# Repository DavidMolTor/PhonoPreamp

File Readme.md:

# Phono Preamplifier

A simple and precise phono preamplifier with a linear power supply.

## Introduction

This project contains the design for a phono preamplifier to be used with moving magnet capsules. It is optimized for low noise and distortion levels and has an accurate RIAA equalization stage.

The project also contains the design of a dual rail linear power supply in order to achive the lowest possible supply noise while keeping costs low.

## Features

 - Compact form factor.

 - Precise RIAA equalization.

 - Low-noise linear power supply.

 - High-performance audio components.

 - Modular design for other applications.

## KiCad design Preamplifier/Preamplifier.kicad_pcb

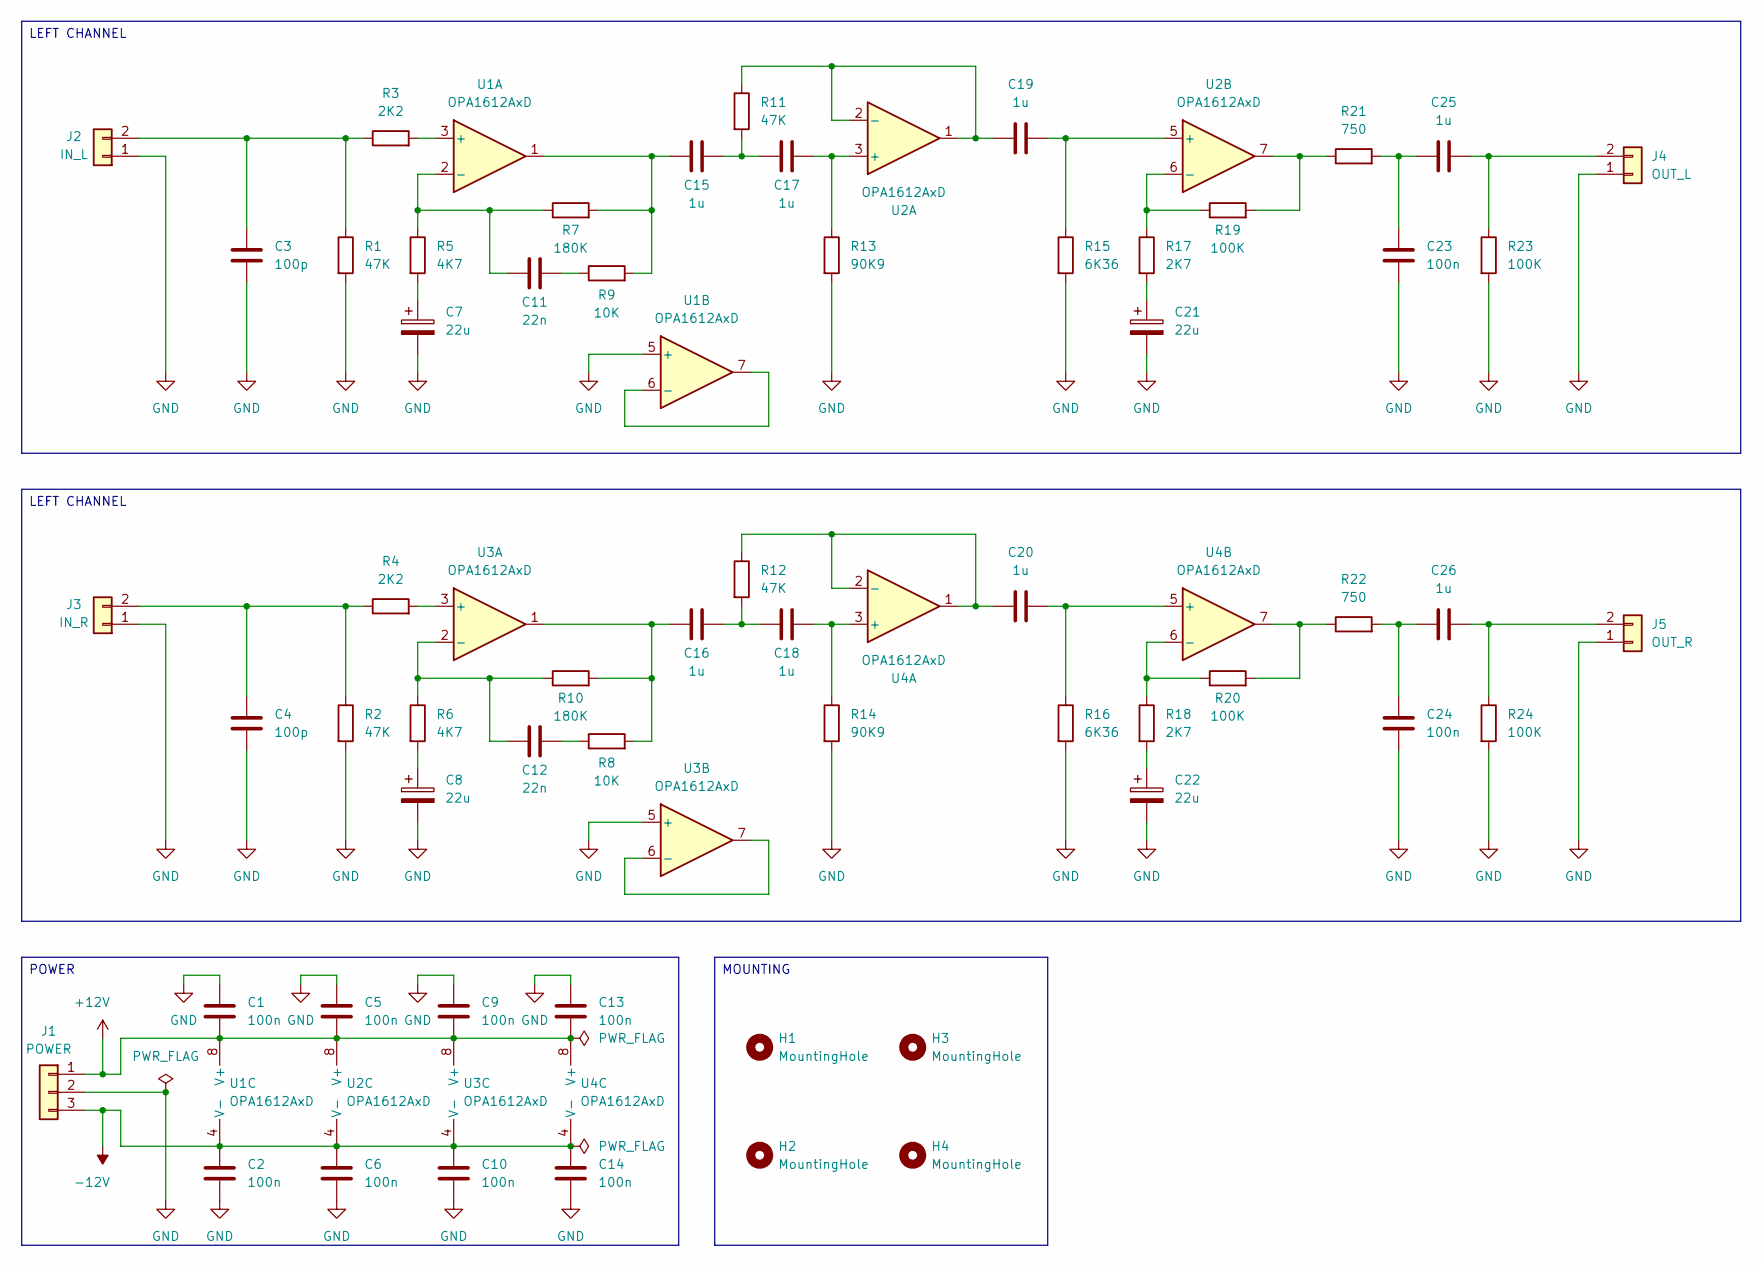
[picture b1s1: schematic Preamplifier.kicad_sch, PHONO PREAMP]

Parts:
C1, C2, C5, C6, C9, C10, C13, C14, C23, C24: 100n; C_0805_2012Metric_Pad1.18x1.45mm_HandSolder
C3, C4: 100p; C_0805_2012Metric_Pad1.18x1.45mm_HandSolder
C7, C8, C21, C22: 22u; CP_Elec_6.3x5.8
C11, C12: 22n; C_0805_2012Metric_Pad1.18x1.45mm_HandSolder
C15, C16, C17, C18, C19, C20, C25, C26: 1u; C_0805_2012Metric_Pad1.18x1.45mm_HandSolder
H1, H2, H3, H4: MountingHole; MountingHole_3.2mm_M3
J1: POWER; Molex_KK-254_1x03_P2.54mm_Vertical
J2: IN_L; Molex_KK-254_1x02_P2.54mm_Vertical
J3: IN_R; Molex_KK-254_1x02_P2.54mm_Vertical
J4: OUT_L; Molex_KK-254_1x02_P2.54mm_Vertical
J5: OUT_R; Molex_KK-254_1x02_P2.54mm_Vertical
R1, R2, R11, R12: 47K; R_0805_2012Metric_Pad1.20x1.40mm_HandSolder
R3, R4: 2K2; R_0805_2012Metric_Pad1.20x1.40mm_HandSolder
R5, R6: 4K7; R_0805_2012Metric_Pad1.20x1.40mm_HandSolder
R7, R10: 180K; R_0805_2012Metric_Pad1.20x1.40mm_HandSolder
R8, R9: 10K; R_0805_2012Metric_Pad1.20x1.40mm_HandSolder
R13, R14: 90K9; R_0805_2012Metric_Pad1.20x1.40mm_HandSolder
R15, R16: 6K36; R_0805_2012Metric_Pad1.20x1.40mm_HandSolder
R17, R18: 2K7; R_0805_2012Metric_Pad1.20x1.40mm_HandSolder
R19, R20, R23, R24: 100K; R_0805_2012Metric_Pad1.20x1.40mm_HandSolder
R21, R22: 750; R_0805_2012Metric_Pad1.20x1.40mm_HandSolder
U1, U2, U3, U4: OPA1612AxD; SOIC-8_3.9x4.9mm_P1.27mm

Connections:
+12V: C1.2, C5.2, C9.2, C13.2, J1.1, U1.8 (V+), U2.8 (V+), U3.8 (V+), U4.8 (V+)
-12V: C2.1, C6.1, C10.1, C14.1, J1.3, U1.4 (V-), U2.4 (V-), U3.4 (V-), U4.4 (V-)
GND: C1.1, C2.2, C3.2, C4.2, C5.1, C6.2, C7.2, C8.2, C9.1, C10.2, C13.1, C14.2, C21.2, C22.2, C23.2, C24.2, J1.2, J2.1, J3.1, J4.1, J5.1, R1.2, R2.2, R13.2, R14.2, R15.2, R16.2, R23.2, R24.2, U1.5 (+), U3.5 (+)
unnamed: C7.1, R5.2
unnamed: C8.1, R6.2
unnamed: C11.2, R9.1
unnamed: C12.2, R8.1
unnamed: C15.1, R7.2, R9.2, U1.1
unnamed: C15.2, C17.1, R11.2
unnamed: C16.1, R8.2, R10.2, U3.1
unnamed: C16.2, C18.1, R12.2
unnamed: C21.1, R17.2
unnamed: C22.1, R18.2
unnamed: C23.1, C25.1, R21.2
unnamed: C24.1, C26.2, R22.2
unnamed: C3.1, J2.2, R1.1, R3.1
unnamed: C4.1, J3.2, R2.1, R4.1
unnamed: C25.2, J4.2, R23.1
unnamed: C26.1, J5.2, R24.1
unnamed: R19.2, R21.1, U2.7
unnamed: R20.2, R22.1, U4.7
unnamed: R3.2, U1.3 (+)
unnamed: C11.1, R5.1, R7.1, U1.2 (-)
unnamed: U1.6 (-), U1.7
unnamed: C17.2, R13.1, U2.3 (+)
unnamed: C19.1, R11.1, U2.1, U2.2 (-)
unnamed: C19.2, R15.1, U2.5 (+)
unnamed: R17.1, R19.1, U2.6 (-)
unnamed: R4.2, U3.3 (+)
unnamed: C12.1, R6.1, R10.1, U3.2 (-)
unnamed: U3.6 (-), U3.7
unnamed: C18.2, R14.1, U4.3 (+)
unnamed: C20.1, R12.1, U4.1, U4.2 (-)
unnamed: C20.2, R16.1, U4.5 (+)
unnamed: R18.1, R20.1, U4.6 (-)

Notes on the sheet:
LEFT CHANNEL
MOUNTING
POWER

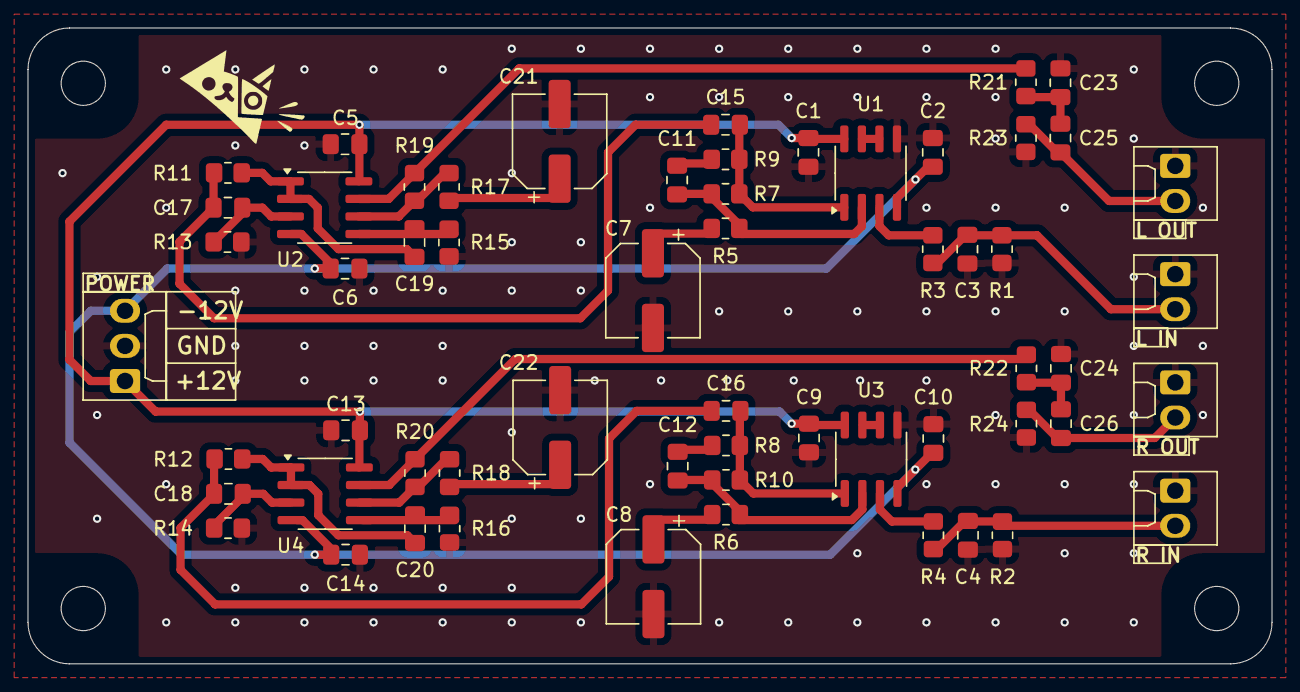
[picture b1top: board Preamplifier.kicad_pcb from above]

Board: 2 copper layers, 90.0 x 46.0 mm, 63 parts (0 on the bottom side), 35 nets.

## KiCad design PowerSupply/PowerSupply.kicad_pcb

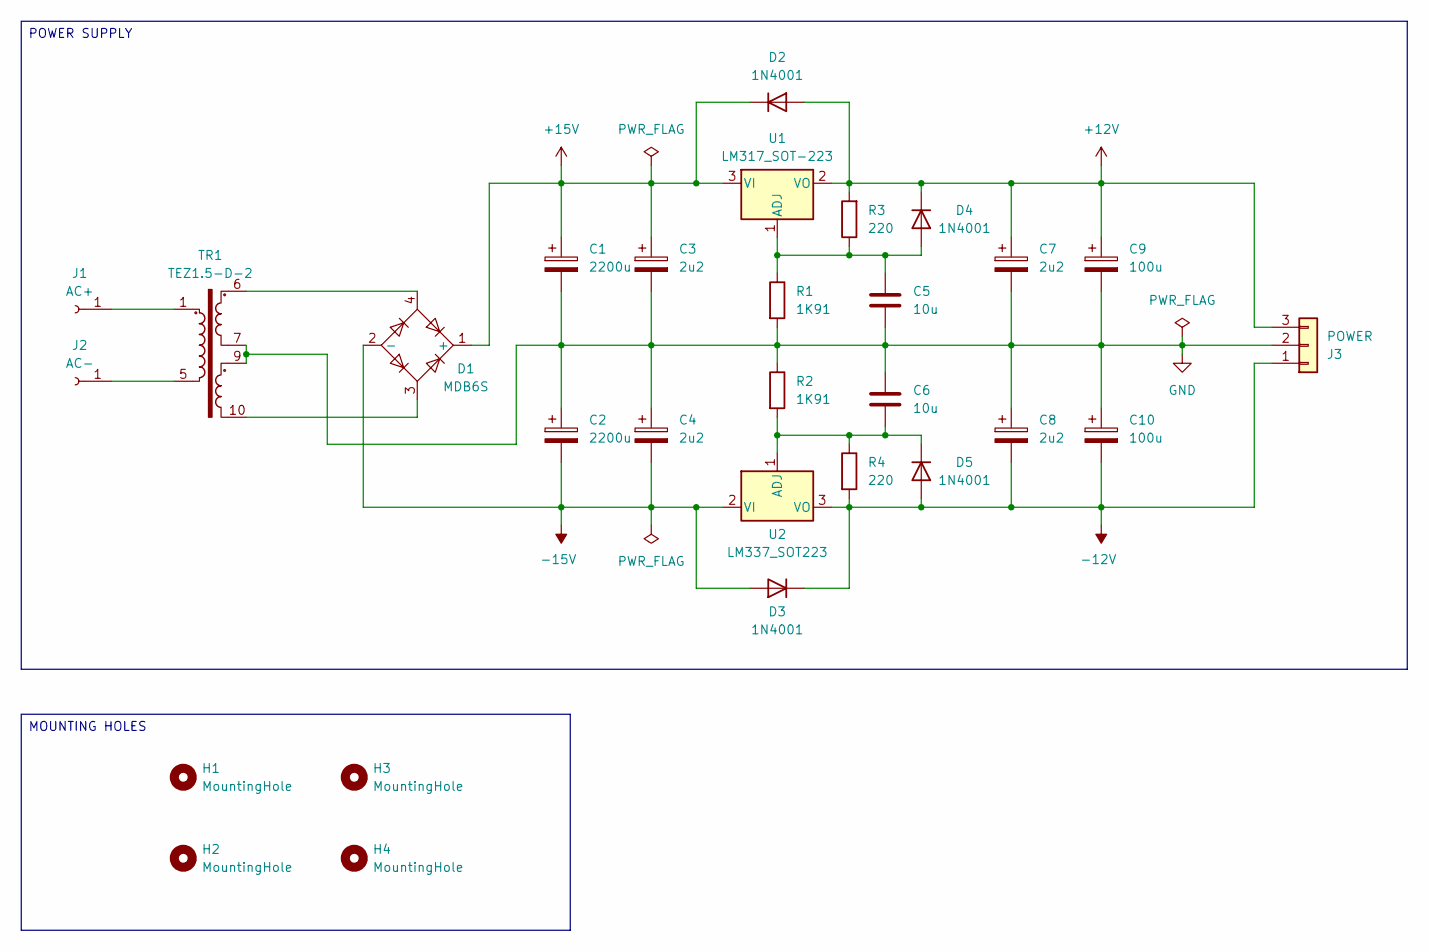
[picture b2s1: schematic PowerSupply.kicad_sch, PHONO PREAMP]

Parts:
C1, C2: 2200u; CP_Elec_16x17.5
C3, C4, C7, C8: 2u2; CP_Elec_4x5.4
C5, C6: 10u; C_0805_2012Metric_Pad1.18x1.45mm_HandSolder
C9, C10: 100u; CP_Elec_6.3x7.7
D1: MDB6S; TSSOP-4_4.4x5mm_P4mm
D2, D3: 1N4001; D_SMA
D4, D5: 1N4001; D_SOD-323
H1, H2, H3, H4: MountingHole; MountingHole_3.2mm_M3
J1: AC+; SolderWire-2.5sqmm_1x01_D2.4mm_OD4.4mm
J2: AC-; SolderWire-2.5sqmm_1x01_D2.4mm_OD4.4mm
J3: POWER; Molex_KK-254_1x03_P2.54mm_Vertical
R1, R2: 1K91; R_0805_2012Metric_Pad1.20x1.40mm_HandSolder
R3, R4: 220; R_0805_2012Metric_Pad1.20x1.40mm_HandSolder
TR1: TEZ1.5-D-2; TRANSFORMER_TEZ-35X42
U1: LM317_SOT-223; SOT-223-3_TabPin2
U2: LM337_SOT223; SOT-223-3_TabPin2

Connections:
+12V: C7.1, C9.1, D2.2 (A), D4.1 (K), J3.3, R3.2, U1.2 (VO)
+15V: C1.1, C3.1, D1.1 (+), D2.1 (K), U1.3 (VI)
-12V: C8.2, C10.2, D3.1 (K), D5.2 (A), J3.1, R4.2, U2.3 (VO)
-15V: C2.2, C4.2, D1.2 (-), D3.2 (A), U2.2 (VI)
GND: C1.2, C2.1, C3.2, C4.1, C5.2, C6.1, C7.2, C8.1, C9.2, C10.1, J3.2, R1.2, R2.1, TR1.7, TR1.9
unnamed: D1.3, TR1.10
unnamed: D1.4, TR1.6
unnamed: C5.1, D4.2 (A), R1.1, R3.1, U1.1 (ADJ)
unnamed: C6.2, D5.1 (K), R2.2, R4.1, U2.1 (ADJ)
unnamed: J1.1, TR1.1
unnamed: J2.1, TR1.5

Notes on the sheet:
POWER SUPPLY
MOUNTING HOLES

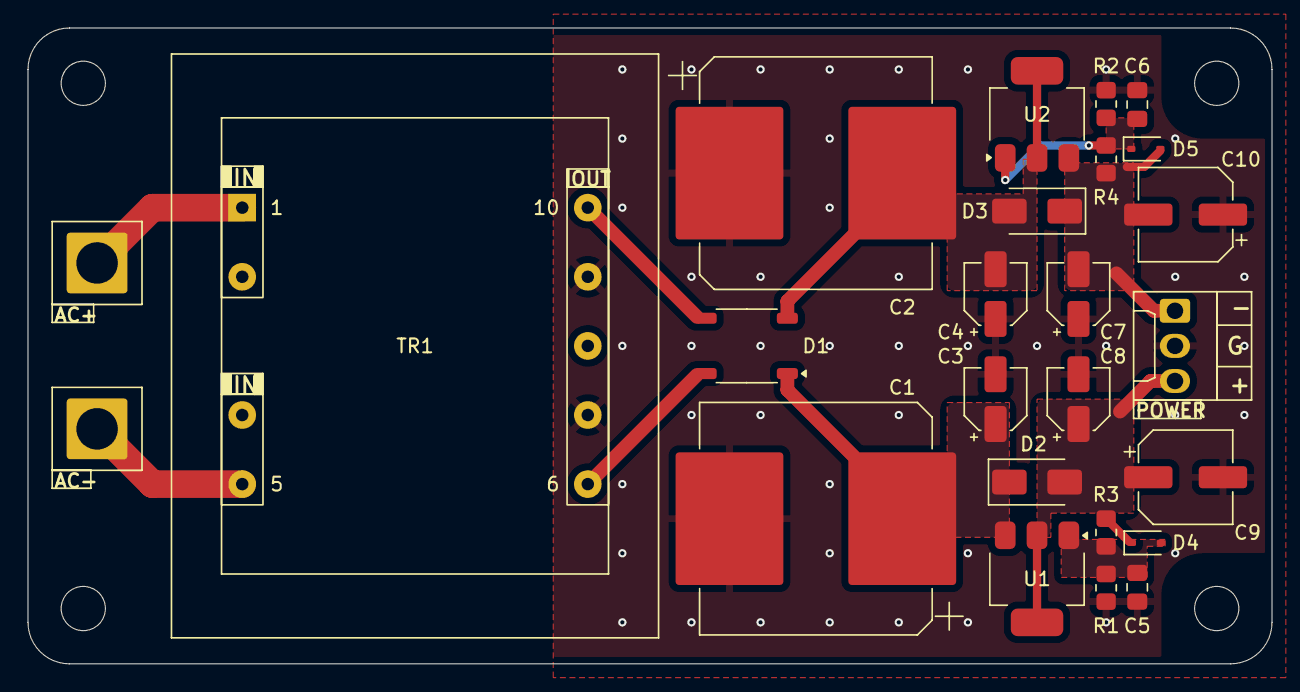
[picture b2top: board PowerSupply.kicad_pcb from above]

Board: 2 copper layers, 90.0 x 46.0 mm, 29 parts (0 on the bottom side), 11 nets.

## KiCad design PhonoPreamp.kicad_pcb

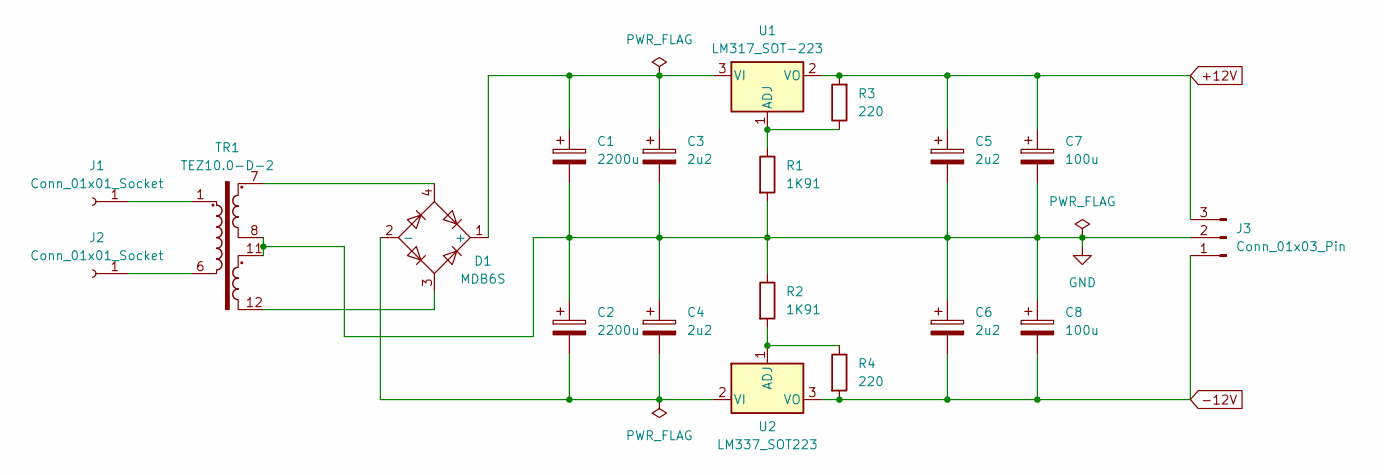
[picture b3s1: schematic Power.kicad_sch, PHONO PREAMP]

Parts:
C1, C2: 2200u; CP_Elec_16x17.5
C3, C4, C5, C6: 2u2; CP_Elec_4x5.4
C7, C8: 100u; CP_Elec_6.3x7.7
D1: MDB6S; TSSOP-4_4.4x5mm_P4mm
J1, J2: Conn_01x01_Socket; SolderWire-2.5sqmm_1x01_D2.4mm_OD4.4mm
J3: Conn_01x03_Pin; Molex_KK-254_AE-6410-03A_1x03_P2.54mm_Vertical
R1, R2: 1K91; R_0805_2012Metric_Pad1.20x1.40mm_HandSolder
R3, R4: 220; R_0805_2012Metric_Pad1.20x1.40mm_HandSolder
TR1: TEZ10.0-D-2; Transformer_Breve_TEZ-44x52
U1: LM317_SOT-223; SOT-223-3_TabPin2
U2: LM337_SOT223; SOT-223-3_TabPin2

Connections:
+12V: C5.1, C7.1, J3.3, R3.2, U1.2 (VO)
-12V: C6.2, C8.2, J3.1, R4.2, U2.3 (VO)
GND: C1.2, C2.1, C3.2, C4.1, C5.2, C6.1, C7.2, C8.1, J3.2, R1.2, R2.1, TR1.8, TR1.11
unnamed: C1.1, C3.1, D1.1 (+), U1.3 (VI)
unnamed: C2.2, C4.2, D1.2 (-), U2.2 (VI)
unnamed: D1.3, TR1.12
unnamed: D1.4, TR1.7
unnamed: J1.1, TR1.1
unnamed: J2.1, TR1.6
unnamed: R1.1, R3.1, U1.1 (ADJ)
unnamed: R2.2, R4.1, U2.1 (ADJ)

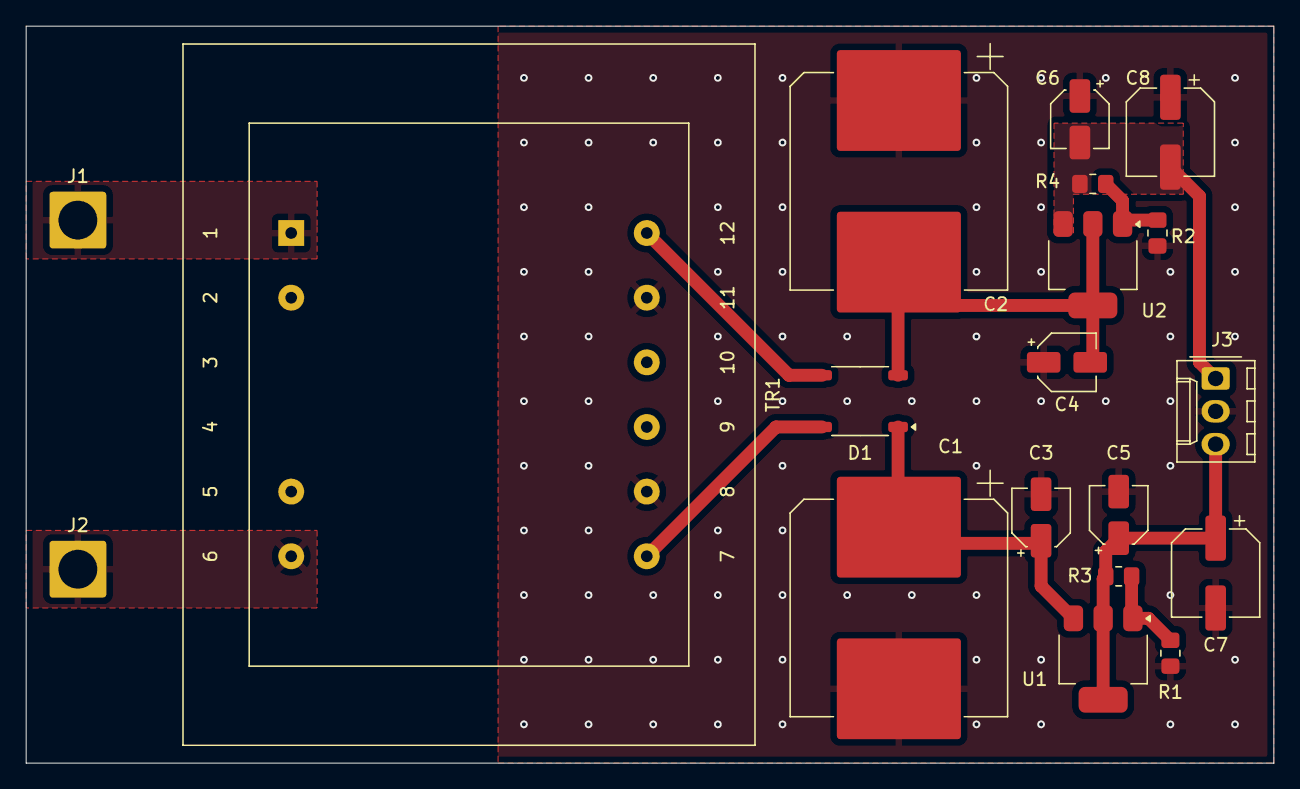
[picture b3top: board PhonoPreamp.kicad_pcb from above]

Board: 2 copper layers, 96.5 x 57.0 mm, 19 parts (0 on the bottom side), 11 nets.

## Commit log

2024-05-15 Updated titles
2024-05-15 Added readme file
2024-05-15 Added simulation project
2024-05-15 Simulation project
    Added all simulation files.
2024-05-16 Removed intial simulations
2024-05-16 Added first preamplifier simulation
2024-05-16 Added second preamplifier simulation
2024-05-16 Added third preamplifier simulation
2024-05-23 Updated ignore filters
2025-08-05 Simulation and PCB Project
    Updated the simulation project.
    Added a PCB design project.
    Deleted unused simulations.
2025-08-06 Project description
    Updated the readme file.
2025-08-06 Main project
    Added new schematic sheets.
    Updated main project.
2025-08-07 Power schematic
    Updated the power schematic sheet.
2025-08-08 Simulation Project
    Updated the simulation project entry.
2025-08-08 Project structure
    Updated the project structure.
    Updated the power supply schematic.
2025-08-08 Power Supply Board
    Updated the power supply schematic.
    Updated the power supply board.
2025-08-08 Preamplifier Simulation
    Updated the preamplifier simulation project.
    Added a simpler preamplifier for testing.
2025-08-08 Preamplifier Simulation
    Updated the preamplifier simulation project.
2025-08-08 Preamplifier Schematic
    Added the preamplifier schematic.
    Updated the preamplifier project.
2025-08-08 Preamplifier Board
    Added a preamplifier channel to the board.
2025-08-08 Power Supply
    Added the power supply board.
2025-08-08 Preamp Schematic
    Added the preamplifier schematic.
2025-08-08 Project Structure
    Updated the project structure.
    Added a preamplifier project.
    Added a power supply project.
2025-08-08 Preamplifier Board
    Added the preamplifier board design.
2025-08-08 Initial Production
    Set the production configuration.
    Updated the preamplifier board design.
2025-08-08 Gerber Ignore
    Updated the gitignore file.
2025-08-09 Production Ready REAL Ready
    Changed C47n to 1206
2025-08-09 READY FOR MANUFACTURING v3
    preamplifier:
    updated silkscreen
    PS ready to manufacturing
2025-08-09 Preamplifier Board
    Updated the preamplifier board design.
2025-08-09 Power Supply Board
    Updated the power supply board design.
2025-08-09 Board Designs
    Updated the power supply board design.
    Updated the preamplifier board design.
2025-08-09 Picture Models
    Added a set of pictures for the power supply board.
    Added a set of pictures for the preamplifier board.
2025-08-09 Update Readme
    Updated the main readme file.
2025-08-10 Preamplifier Design
    Updated the preamplifier board design.
2025-08-11 Power Supply Design
    Updated the power supply schematic.
    Updated the power supply board design.
    Set the power supply project version to 1.1.
2025-08-12 Power Supply Design
    Updated the power supply board design.
2025-08-12 Board 3D Models
    Added a 3D model for the power supply board.
    Added a 3D model for the preamplifier board.
2025-10-29 Preamplifier Board
    Updated the preamplifier schematic.
    Updated the preamplifier board design.
2026-02-07 Company name
    Updated the company name for all project files.
